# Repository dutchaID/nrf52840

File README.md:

# Dokumentasi Board NRF52840 V1.0723

﷽

Semoga sehat selalu untuk kita semua.
.
.
.
.
.

# Flash bootloader NRF52840

Bootloader diperlukan karena SOC **NRF52840** dari JLC masih kosong, jadi  fitur-fitur yang ada seperti DFU USB tidak dapat terbaca di PC.

File bootloader bisa menggunakan apa saja, sebagai contoh saya menggunakan bootloader **NRF52840 DK** (PCA10056), kemudian semua config pinout mengikuti board tersebut.

## Peralatan Tempur

- OpenOCD, [gas di sini](https://openocd.org/).
- ST-link V.2
- File bootloader PCA10056
- Arduino IDE, [gas di sini](https://www.arduino.cc/en/software).
- Kabel USB type C

## Langkah-Langkah

1. Install semua peralatan tempurnya. Pastikan sudah **OK** ya...
2. Hubungkan board `NRF52840` dengan `ST-Link V.2` via SWD.
	> */3V3*
	> */GND*
	> */SWCLK*
	> */SWDIO/*
3. Buka Terminal:
    - Cek versi `openocd`,
       >*> openocd -v*
    - Run `openocd`, direktori nya disesuaikan ya...
       >*> openocd -f share/openocd/scripts/interface/stlink.cfg -f share/openocd/scripts/target/nrf52.cfg*
    - `Openocd` sekarang sudah running. Sekarang kita buka terminal lagi untuk menggunakan `telnet`.
       >*> telnet localhost 4444*
    - `Stop execution` bisa gunakan, 
       > *> halt*
    - Hapus `flash` memory,
       > *> nrf5 mass_erase*
    - `Flash NRF52840`,
       > *> program /your/path/to/the/pca10056_bootloader-0.6.2_s140_6.1.1.hex verify*
    - Resume the execution,
       > *> resume*
       
4. Jika berhasil maka pada `Device Manager`, board akan terbaca sebagai *`USB Serial Device(COM...)`*
5. Untuk masuk ke mode `DFU` tekan 2 kali tombol `reset`.

## Pemrograman NRF52840 menggunakan Arduino IDE
1. Buka Arduino IDE, lalu pilih tab `File` dan pilih `Preferences` dan masukkan URL berikut:
    >*https://adafruit.github.io/arduino-board-index/package_adafruit_index.json*
2. Restart Arduino IDE.
3. Pilih `Tools` > `Board` > `Board Manager`. Kemudian pada textbox filter pencarian filter dengan `NRF` dan install `Arduino nRF52 Boars` dan `Adafruit nRF52`.
4. Setelah selesai, silahkan digasken ngodingnya... (saya mencoba dengan program template `bleuart`).....

## Config Pin Board NRF52840

- On board LED `P0.11`, active `LOW`.
- On board button `P1.10`, active `LOW`.
- Switch RF PE4259 `P1.06`, active `HIGH`, lebih detail lihat datasheet.
- Front end RF RFX2401C, RX Enable `P1.04` dan TX Enable `P1.05`, lebih detail lihat datasheet.

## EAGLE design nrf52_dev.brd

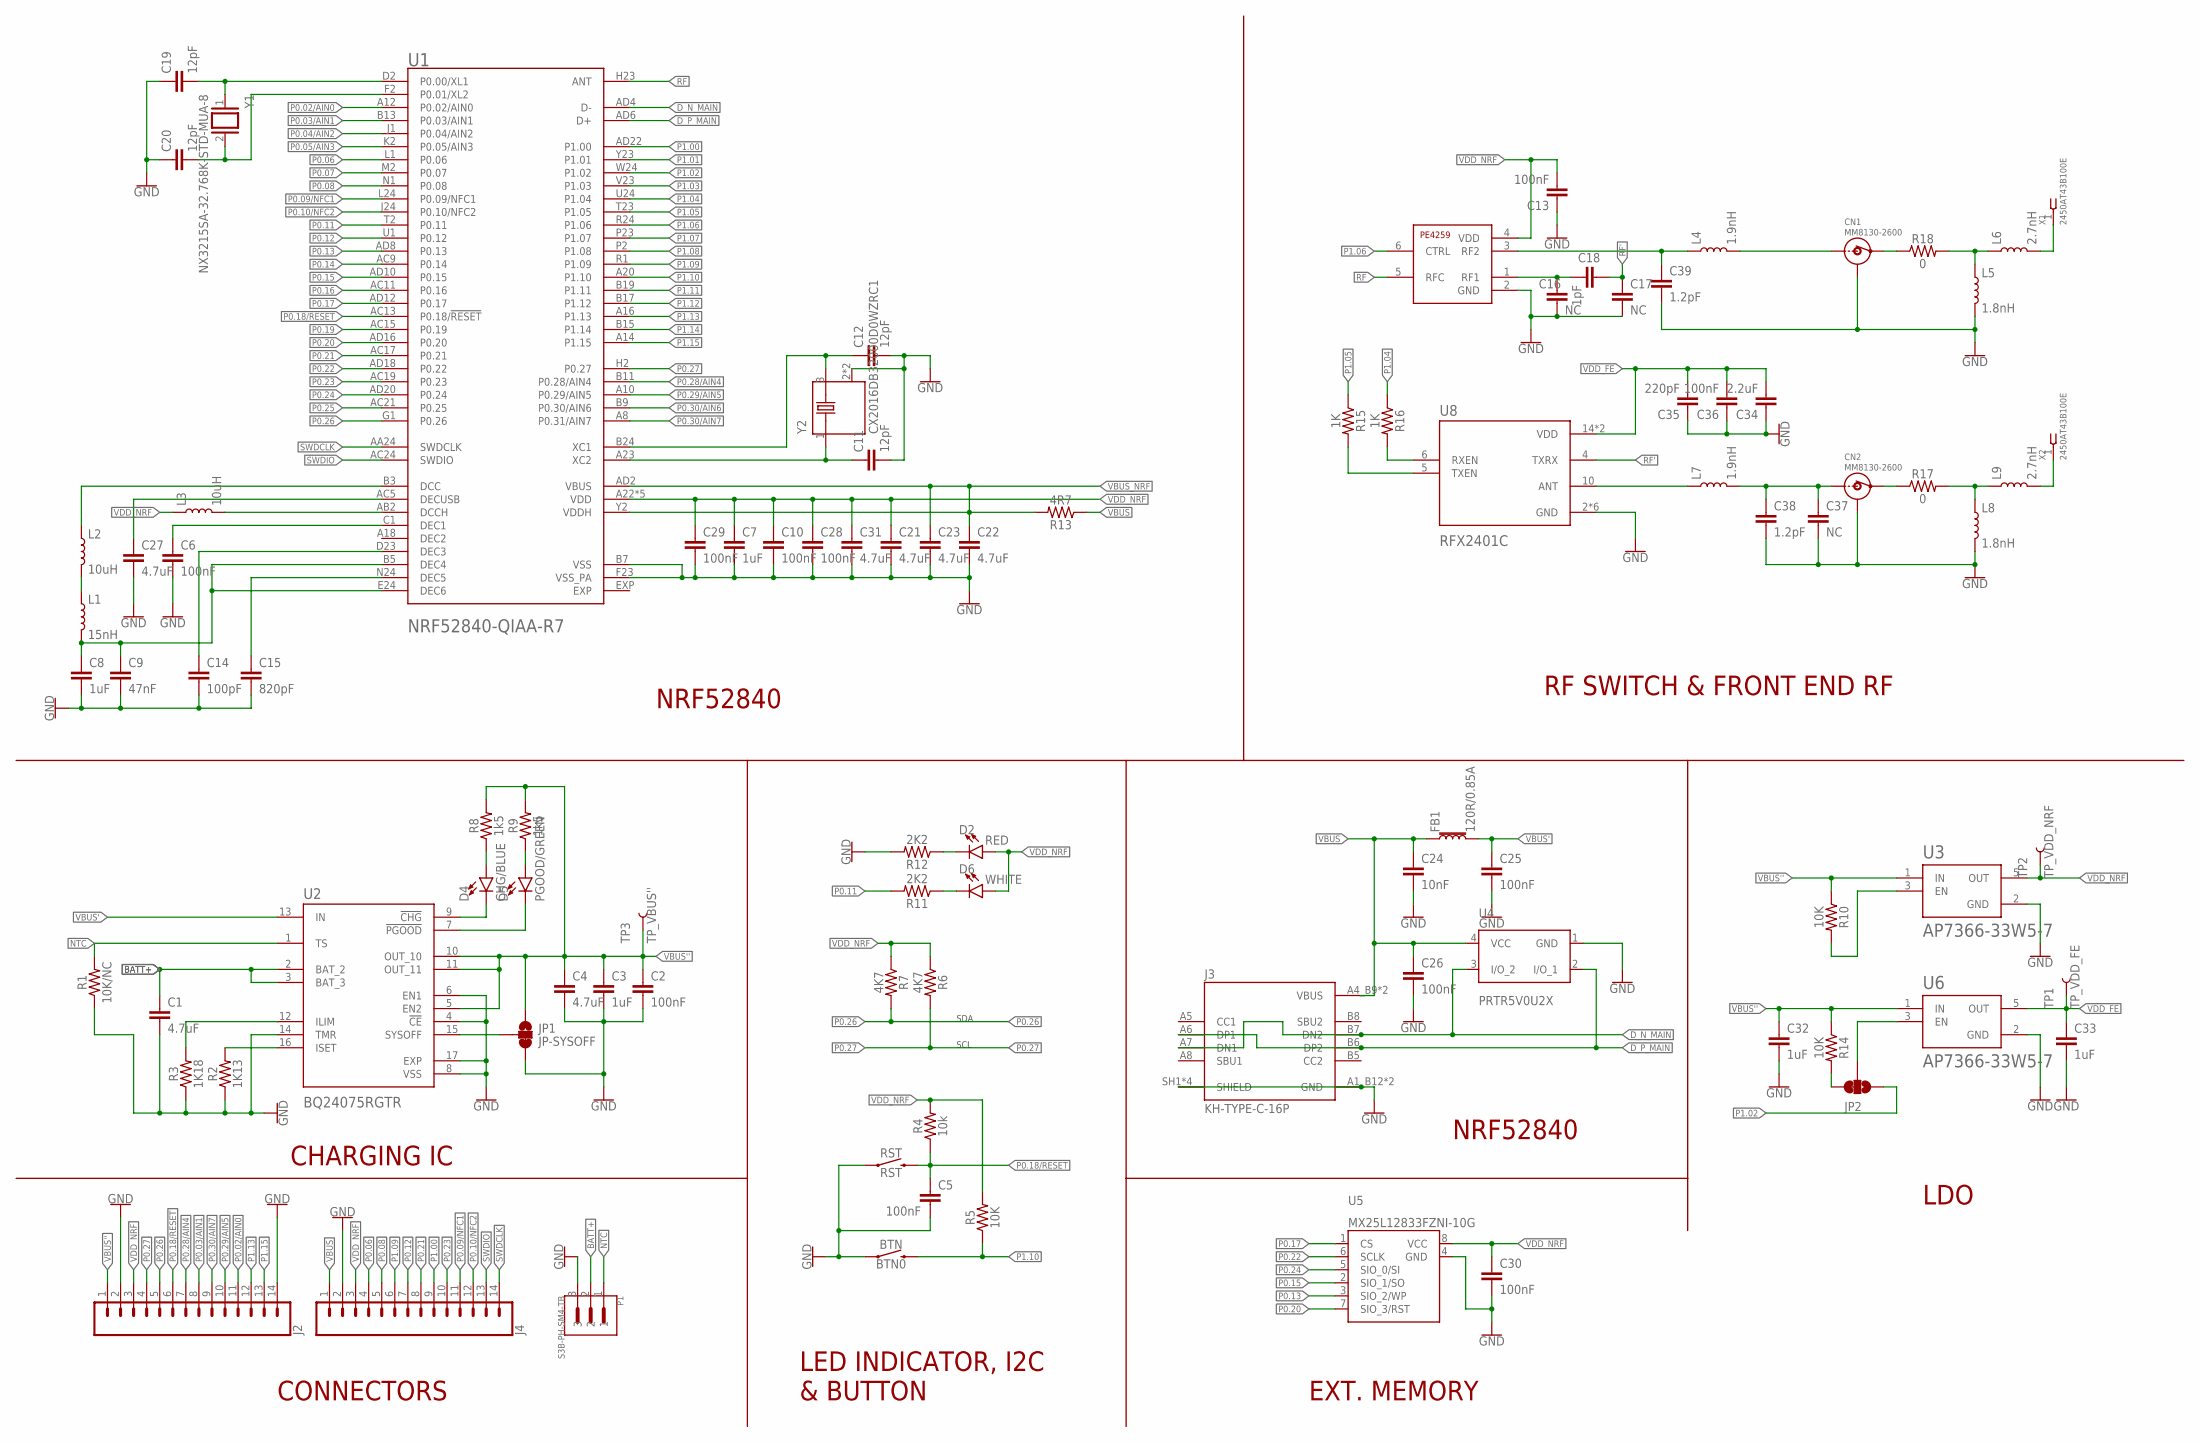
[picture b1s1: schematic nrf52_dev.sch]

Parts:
BTN: BTN0; TACTILE_SWITCH_SMD_6.0X3.5MM
C1, C4: 4.7uF; 0805
C2: 100nF; 0603
C3, C32, C33: 1uF; 0603
C5, C6, C10, C13, C25, C26, C28, C29, C30, C36: 100nF; 0402
C7, C8: 1uF; 0402
C9: 47nF; 0402
C11, C12: 12pF; 0603
C14: 100pF; 0402
C15: 820pF; 0402
C16, C17, C37: NC; 0402
C18: 1pF; 0603
C19, C20: 12pF; 0402
C21, C22, C23, C31: 4.7uF; 0402
C24: 10nF; 0402
C27: 4.7uF; 0603
C34: 2.2uF; 0402
C35: 220pF; 0402
C38, C39: 1.2pF; 0402
CN1, CN2: MM8130-2600
D2: RED; LED-0603
D4: CHG/BLUE; LED-0603
D5: PGOOD/GREEN; LED-0603
D6: WHITE; LED-0603
FB1: 120R/0.85A; 0402
J2, J4: CONN_14NO_SILK; 1X14_NO_SILK
J3: KH-TYPE-C-16P; KINGHELM_KH-TYPE-C-16P
JP1: JP-SYSOFF; SMT-JUMPER_3_1-NC_TRACE_SILK
JP2: JP_EN1; SMT-JUMPER_3_1-NC_TRACE_SILK
L1: 15nH; 0402
L2, L3: 10uH; 0603
L4, L7: 1.9nH; 0402
L5, L8: 1.8nH; 0603
L6, L9: 2.7nH; 0603
P1: S3B-PH-SM4-TB; JST_S3B-PH-SM4-TB
R1: 10K/NC; 0603
R2: 1K13; 0603
R3: 1K18; 0603
R4: 10k; 0402
R5: 10K; 0402
R6, R7: 4K7; 0402
R8, R9: 1k5; 0402
R10, R14: 10K; 0603
R11, R12: 2K2; 0402
R13: 4R7; 0603
R15, R16: 1K; 0402
R17, R18: 0; 0402
RST: RST; TACTILE_SWITCH_SMD_6.0X3.5MM
TP1: TP_VDD_FE; PAD.03X.04
TP2: TP_VDD_NRF; PAD.03X.04
TP3: TP_VBUS''; PAD.03X.04
U1: NRF52840-QIAA-R7; NORDIC_NRF52840-QIAA-R7
U2: BQ24075RGTR; QFN50P300X300X100-17N
U3, U6: AP7366-33W5-7; SOT95P285X140-5N
U4: PRTR5V0U2X; SOT190P230X110-4N
U5: MX25L12833FZNI-10G; SON127P500X600X80-9N
U7: PE4259; SOT65P210X110-6N
U8: RFX2401C; QFN50P300X300X60-17N
X1, X2: 2450AT43B100E; 2450AT43B100
Y1: NX3215SA-32.768K-STD-MUA-8; XTAL_NX3215SA-32.768K-STD-MUA-8
Y2: CX2016DB32000D0WZRC1; OSCCC200X160X45N

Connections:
BATT+: C1.1, P1.2, U2.2 (BAT_2), U2.3 (BAT_3)
DEC2: U1.A18 (DEC2)
D_N_MAIN: J3.A7 (DN1), J3.B7 (DN2), U1.AD4 (D-), U4.3 (I/O_2)
D_P_MAIN: J3.A6 (DP1), J3.B6 (DP2), U1.AD6 (D+), U4.2 (I/O_1)
EXP: U1.EXP
GND: BTN.1, C1.2, C2.2, C3.2, C4.2, C5.2, C6.2, C7.2, C8.2, C9.2, C10.2, C11.2, C12.2, C13.1, C14.2, C15.2, C16.2, C17.2, C19.1, C20.1, C21.2, C22.2, C23.2, C24.2, C25.2, C26.2, C27.2, C28.2, C29.2, C30.2, C31.2, C32.2, C33.2, C34.1, C35.1, C36.1, C37.2, C38.2, C39.2, CN1.1, CN1.2, CN1.3, CN1.4, CN2.1, CN2.2, CN2.3, CN2.4, J2.2, J2.14, J3.A1_B12 (GND), J3.A12_B1 (GND), J3.SH1 (SHIELD), J3.SH2 (SHIELD), J3.SH3 (SHIELD), J3.SH4 (SHIELD), J4.2, JP1.3, L5.2, L8.2, P1.3, R1.1, R2.1, R3.1, R12.2, RST.1, U1.B7 (VSS), U1.F23 (VSS_PA), U2.4 (!CE), U2.6 (EN1), U2.8 (VSS), U2.14 (TMR), U2.17 (EXP), U3.2 (GND), U4.1 (GND), U5.4 (GND), U6.2 (GND), U7.2 (GND), U8.2 (GND), U8.3 (GND), U8.8 (GND), U8.9 (GND), U8.11 (GND), U8.17 (GND), Y2.2 (GND), Y2.4 (GND)
unnamed: JP2.2, U6.3 (EN)
unnamed: C27.1, U1.AC5 (DECUSB)
unnamed: JP2.3, R14.2
unnamed: D4.C, U2.9 (!CHG)
unnamed: L3.2, U1.AB2 (DCCH)
unnamed: L1.1, L2.2
unnamed: C6.1, U1.C1 (DEC1)
unnamed: L2.1, U1.B3 (DCC)
unnamed: C20.2, U1.F2 (P0.01/XL2), Y1.2
unnamed: C14.1, U1.D23 (DEC3)
unnamed: C15.1, U1.N24 (DEC5)
unnamed: C8.1, C9.1, L1.2, U1.B5 (DEC4), U1.E24 (DEC6)
unnamed: C19.2, U1.D2 (P0.00/XL1), Y1.1
unnamed: C11.1, U1.A23 (XC2), Y2.1 (HOT_1)
unnamed: C12.1, U1.B24 (XC1), Y2.3 (HOT_3)
unnamed: R16.2, U8.6 (RXEN)
unnamed: R15.2, U8.5 (TXEN)
unnamed: D6.C, R11.1
unnamed: D5.C, U2.7 (!PGOOD)
unnamed: R10.2, U3.3 (EN)
unnamed: D2.C, R12.1
unnamed: C16.1, C18.2, U7.1 (RF1)
unnamed: CN1.OUT, R18.1
unnamed: R2.2, U2.16 (ISET)
unnamed: L5.1, L6.1, R18.2
unnamed: JP1.2, U2.15 (SYSOFF)
unnamed: L6.2, X1.1
unnamed: R3.2, U2.12 (ILIM)
unnamed: D4.A, R8.1
unnamed: D5.A, R9.1
unnamed: CN1.IN, L4.2
unnamed: C39.1, L4.1, U7.3 (RF2)
unnamed: C37.1, C38.1, CN2.IN, L7.2
unnamed: CN2.OUT, R17.1
unnamed: L8.1, L9.1, R17.2
unnamed: L9.2, X2.1
unnamed: L7.1, U8.10 (ANT)
NTC: P1.1, R1.2, U2.1 (TS)
P0.02/AIN0: J2.11, U1.A12 (P0.02/AIN0)
P0.03/AIN1: J2.8, U1.B13 (P0.03/AIN1)
P0.04/AIN2: U1.J1 (P0.04/AIN2)
P0.05/AIN3: U1.K2 (P0.05/AIN3)
P0.06: J4.4, U1.L1 (P0.06)
P0.07: U1.M2 (P0.07)
P0.08: J4.5, U1.N1 (P0.08)
P0.09/NFC1: J4.11, U1.L24 (P0.09/NFC1)
P0.10/NFC2: J4.12, U1.J24 (P0.10/NFC2)
P0.11: R11.2, U1.T2 (P0.11)
P0.12: J4.7, U1.U1 (P0.12)
P0.13: U1.AD8 (P0.13), U5.3 (SIO_2/WP)
P0.14: U1.AC9 (P0.14)
P0.15: U1.AD10 (P0.15), U5.2 (SIO_1/SO)
P0.16: U1.AC11 (P0.16)
P0.17: U1.AD12 (P0.17), U5.1 (CS)
P0.18/RESET: C5.1, J2.6, R4.1, RST.2, U1.AC13 (P0.18/!RESET)
P0.19: U1.AC15 (P0.19)
P0.20: U1.AD16 (P0.20), U5.7 (SIO_3/RST)
P0.21: J4.8, U1.AC17 (P0.21)
P0.22: U1.AD18 (P0.22), U5.6 (SCLK)
P0.23: J4.10, U1.AC19 (P0.23)
P0.24: U1.AD20 (P0.24), U5.5 (SIO_0/SI)
P0.25: U1.AC21 (P0.25)
P0.26: J2.5, R7.2, U1.G1 (P0.26)
P0.27: J2.4, R6.2, U1.H2 (P0.27)
P0.28/AIN4: J2.7, U1.B11 (P0.28/AIN4)
P0.29/AIN5: J2.10, U1.A10 (P0.29/AIN5)
P0.30/AIN6: U1.B9 (P0.30/AIN6)
P0.30/AIN7: J2.9, U1.A8 (P0.31/AIN7)
P1.00: J4.9, U1.AD22 (P1.00)
P1.01: U1.Y23 (P1.01)
P1.02: JP2.1, U1.W24 (P1.02)
P1.03: U1.V23 (P1.03)
P1.04: R16.1, U1.U24 (P1.04)
P1.05: R15.1, U1.T23 (P1.05)
P1.06: U1.R24 (P1.06), U7.6 (CTRL)
P1.07: U1.P23 (P1.07)
P1.08: U1.P2 (P1.08)
P1.09: J4.6, U1.R1 (P1.09)
P1.10: BTN.2, R5.1, U1.A20 (P1.10)
P1.11: U1.B19 (P1.11)
P1.12: U1.B17 (P1.12)
P1.13: J2.12, U1.A16 (P1.13)
P1.14: U1.B15 (P1.14)
P1.15: J2.13, U1.A14 (P1.15)
RF: U1.H23 (ANT), U7.5 (RFC)
RF': C17.1, C18.1, U8.4 (TXRX)
SWDCLK: J4.14, U1.AA24 (SWDCLK)
SWDIO: J4.13, U1.AC24 (SWDIO)
VBUS: C24.1, C26.1, FB1.1, J3.A4_B9 (VBUS), J3.A9_B4 (VBUS), J4.1, R13.1, U4.4 (VCC)
VBUS': C25.1, FB1.2, U2.13 (IN)
VBUS'': C2.1, C3.1, C4.1, C32.1, J2.1, JP1.1, R8.2, R9.2, R10.1, R14.1, TP3.P$1, U2.5 (EN2), U2.10 (OUT_10), U2.11 (OUT_11), U3.1 (IN), U6.1 (IN)
VBUS_NRF: C22.1, C23.1, R13.2, U1.AD2 (VBUS), U1.Y2 (VDDH)
VDD_FE: C33.1, C34.2, C35.2, C36.2, TP1.P$1, U6.5 (OUT), U8.14 (VDD), U8.16 (VDD)
VDD_NRF: C7.1, C10.1, C13.2, C21.1, C28.1, C29.1, C30.1, C31.1, D2.A, D6.A, J2.3, J4.3, L3.1, R4.2, R5.2, R6.1, R7.1, TP2.P$1, U1.A22 (VDD), U1.AD14 (VDD), U1.AD23 (VDD), U1.B1 (VDD), U1.W1 (VDD), U3.5 (OUT), U5.8 (VCC), U7.4 (VDD)

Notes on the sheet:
SDA
SCL
NRF52840
RF SWITCH & FRONT END RF
CHARGING IC
CONNECTORS
LED INDICATOR, I2C & BUTTON
LDO
EXT. MEMORY

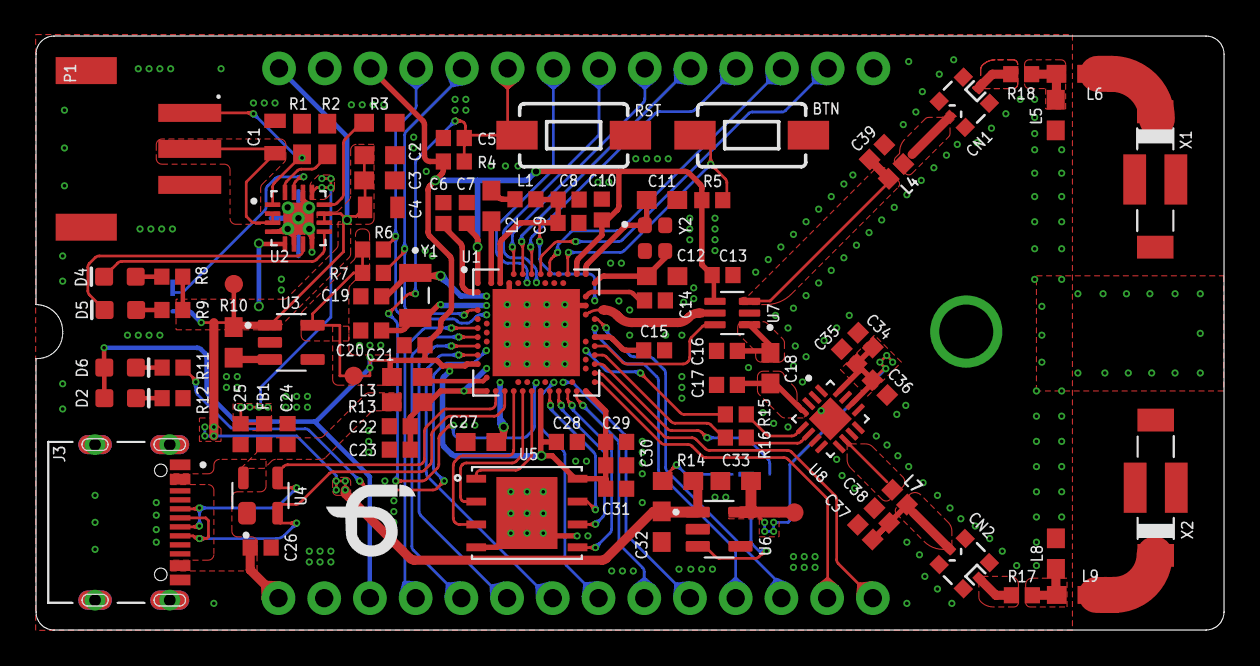
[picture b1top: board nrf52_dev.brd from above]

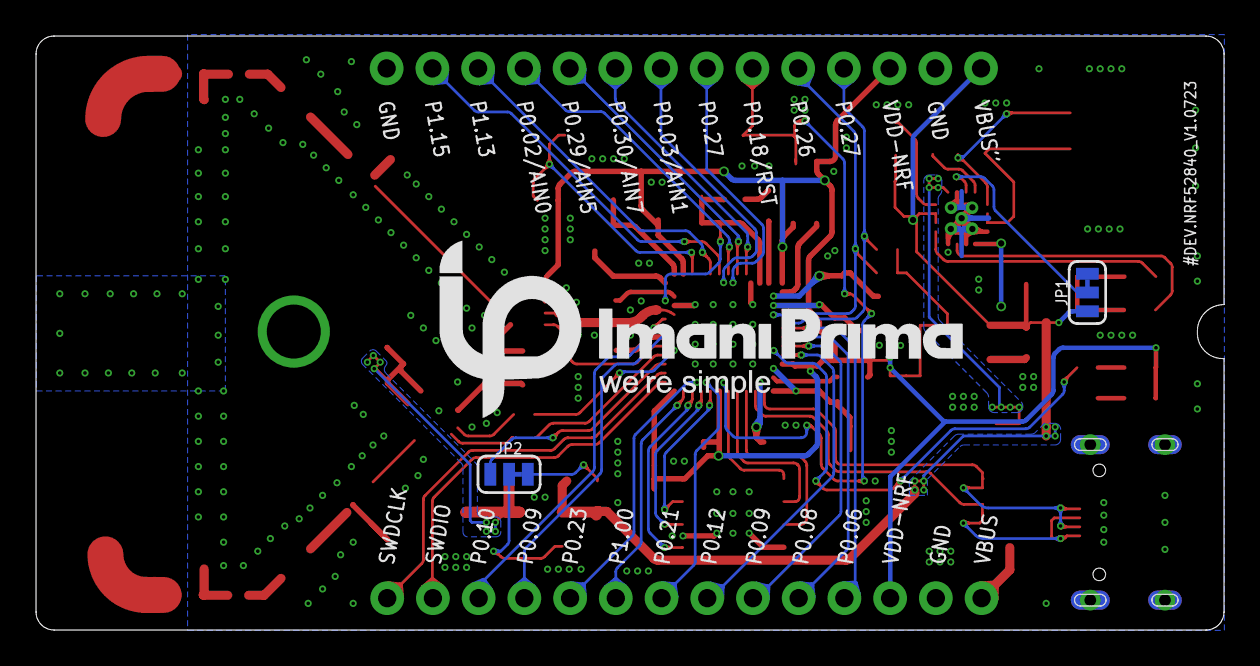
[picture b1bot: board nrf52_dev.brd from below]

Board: 2 copper layers, 66.0 x 33.0 mm, 98 parts (3 on the bottom side), 83 nets.

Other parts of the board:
U$1: IP_S
U$3: IPS

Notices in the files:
parts and their libraries:
SparkFun-Capacitors: Licensing: Creative Commons ShareAlike 4.0 International - https://creativecommons.org/licenses/by-sa/4.0
